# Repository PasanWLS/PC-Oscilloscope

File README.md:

# PC-Oscilloscope
PC Oscilloscope designing
this is our 3rd year final project, pc oscilloscope

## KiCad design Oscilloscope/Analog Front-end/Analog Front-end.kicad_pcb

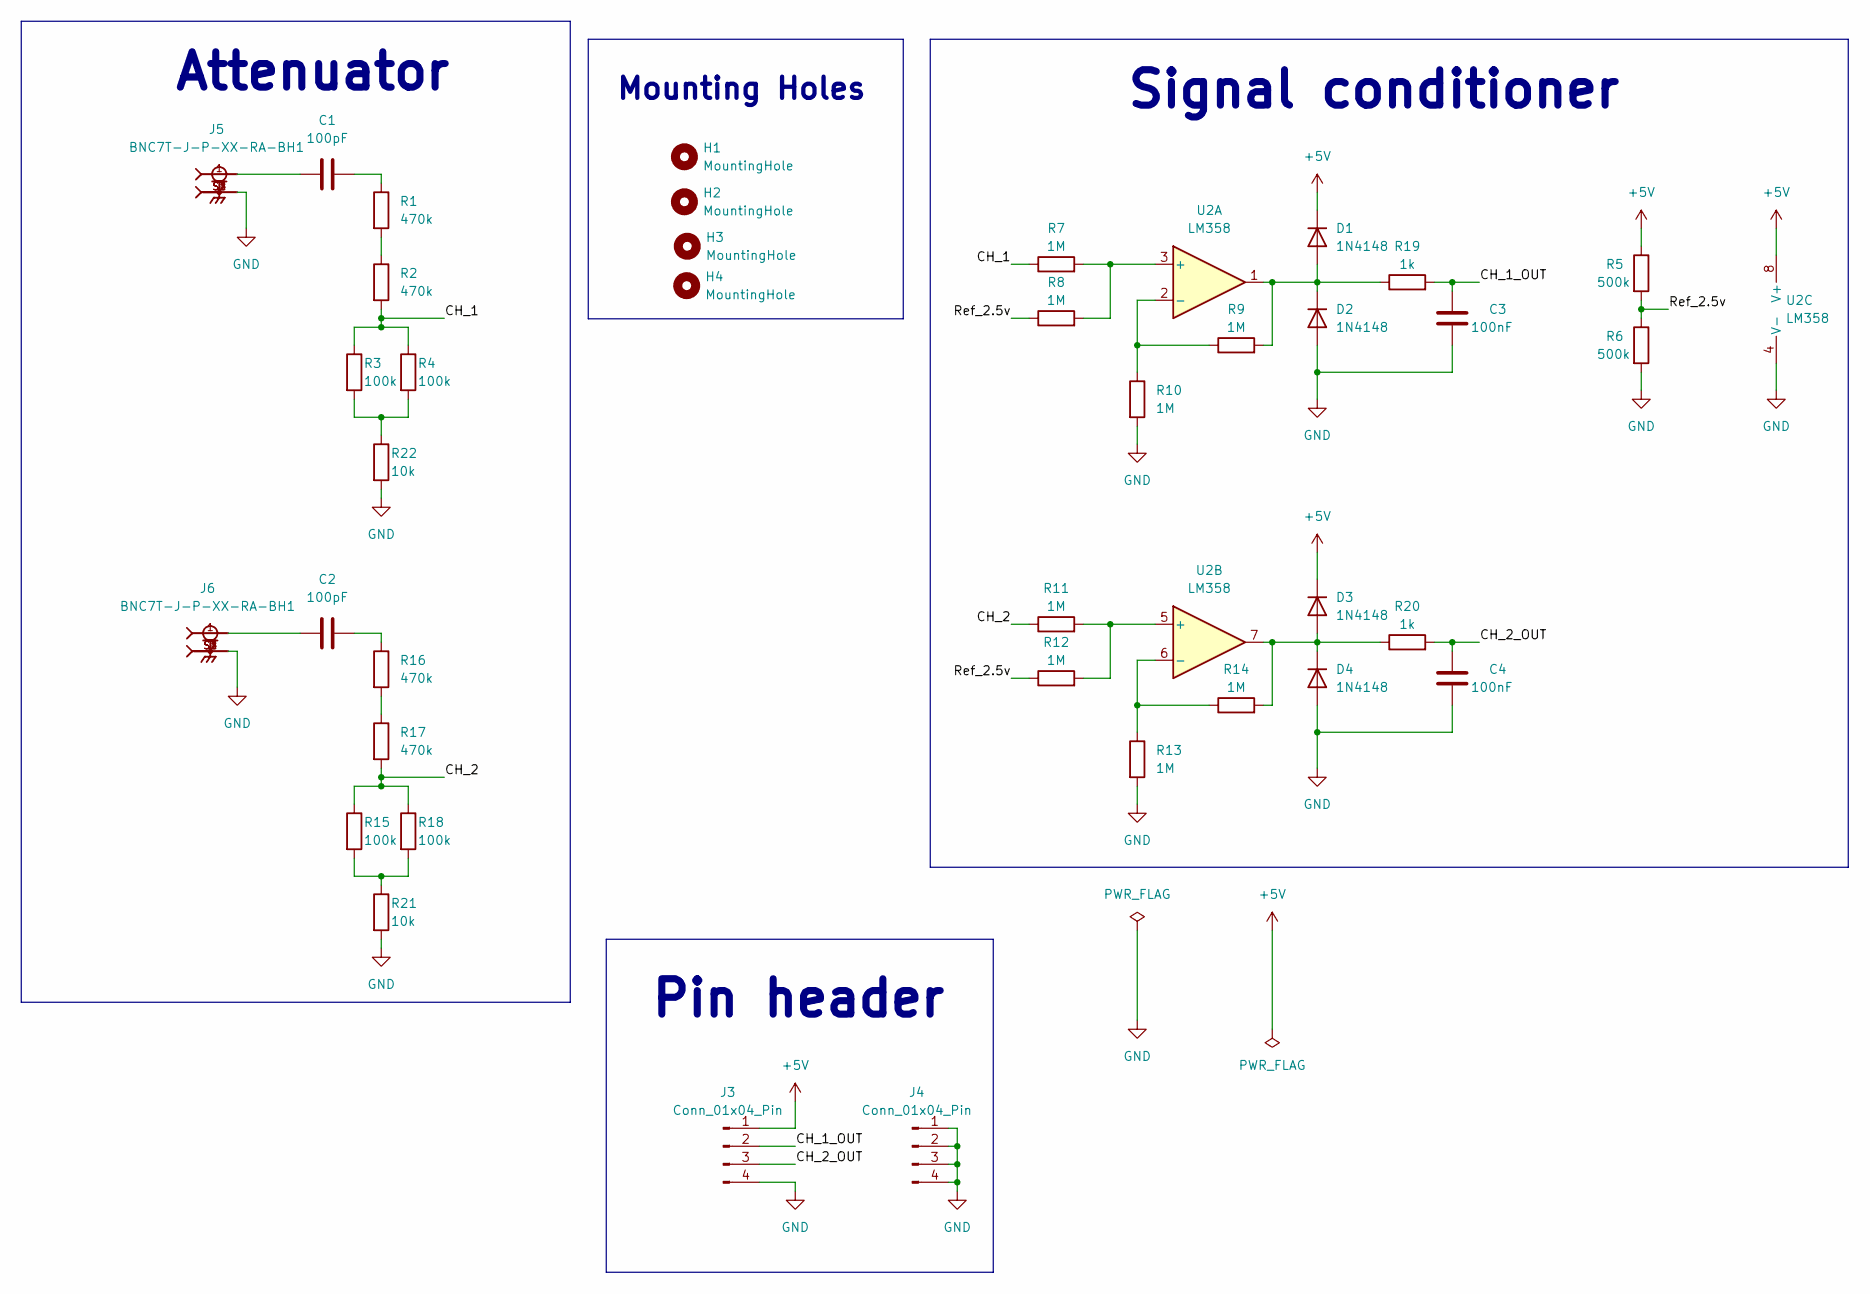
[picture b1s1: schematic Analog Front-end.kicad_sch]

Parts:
C1, C2: 100pF; C_Disc_D3.8mm_W2.6mm_P2.50mm
C3, C4: 100nF; C_Disc_D3.8mm_W2.6mm_P2.50mm
D1, D2, D3, D4: 1N4148; D_DO-35_SOD27_P7.62mm_Horizontal
H1, H2, H3, H4: MountingHole; MountingHole_2.2mm_M2
J3, J4: Conn_01x04_Pin; PinHeader_1x04_P2.54mm_Vertical
J5, J6: BNC7T-J-P-XX-RA-BH1; SAMTEC_BNC7T-J-P-XX-RA-BH1; PARTREV G
R1, R2, R16, R17: 470k; R_Axial_DIN0207_L6.3mm_D2.5mm_P10.16mm_Horizontal
R3, R4, R15, R18: 100k; R_Axial_DIN0207_L6.3mm_D2.5mm_P10.16mm_Horizontal
R5, R6: 500k; R_Axial_DIN0207_L6.3mm_D2.5mm_P10.16mm_Horizontal
R7, R8, R9, R10, R11, R12, R13, R14: 1M; R_Axial_DIN0207_L6.3mm_D2.5mm_P10.16mm_Horizontal
R19, R20: 1k; R_Axial_DIN0207_L6.3mm_D2.5mm_P10.16mm_Horizontal
R21, R22: 10k; R_Axial_DIN0207_L6.3mm_D2.5mm_P10.16mm_Horizontal
U2: LM358; DIP-8_W7.62mm

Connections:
+5V: D1.1 (K), D3.1 (K), J3.1, R5.1, U2.8 (V+)
/CH_1: R2.2, R3.1, R4.1, R7.1
/CH_1_OUT: C3.2, J3.2, R19.2
/CH_2: R11.1, R15.1, R17.2, R18.1
/CH_2_OUT: C4.2, J3.3, R20.2
/Ref_2.5v: R5.2, R6.1, R8.1, R12.1
GND: C3.1, C4.1, D2.2 (A), D4.2 (A), J3.4, J4.1, J4.2, J4.3, J4.4, J5.S1, J5.S2, J5.S3, J5.S4, J6.S1, J6.S2, J6.S3, J6.S4, R6.2, R10.2, R13.2, R21.2, R22.2, U2.4 (V-)
unnamed: C1.1, J5.1
unnamed: C1.2, R1.1
unnamed: C2.1, J6.1
unnamed: C2.2, R16.1
unnamed: D1.2 (A), D2.1 (K), R9.2, R19.1, U2.1
unnamed: D3.2 (A), D4.1 (K), R14.2, R20.1, U2.7
unnamed: R1.2, R2.1
unnamed: R15.2, R18.2, R21.1
unnamed: R16.2, R17.1
unnamed: R3.2, R4.2, R22.1
unnamed: R7.2, R8.2, U2.3 (+)
unnamed: R9.1, R10.1, U2.2 (-)
unnamed: R11.2, R12.2, U2.5 (+)
unnamed: R13.1, R14.1, U2.6 (-)

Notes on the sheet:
Mounting Holes
Signal conditioner
Attenuator
Pin header

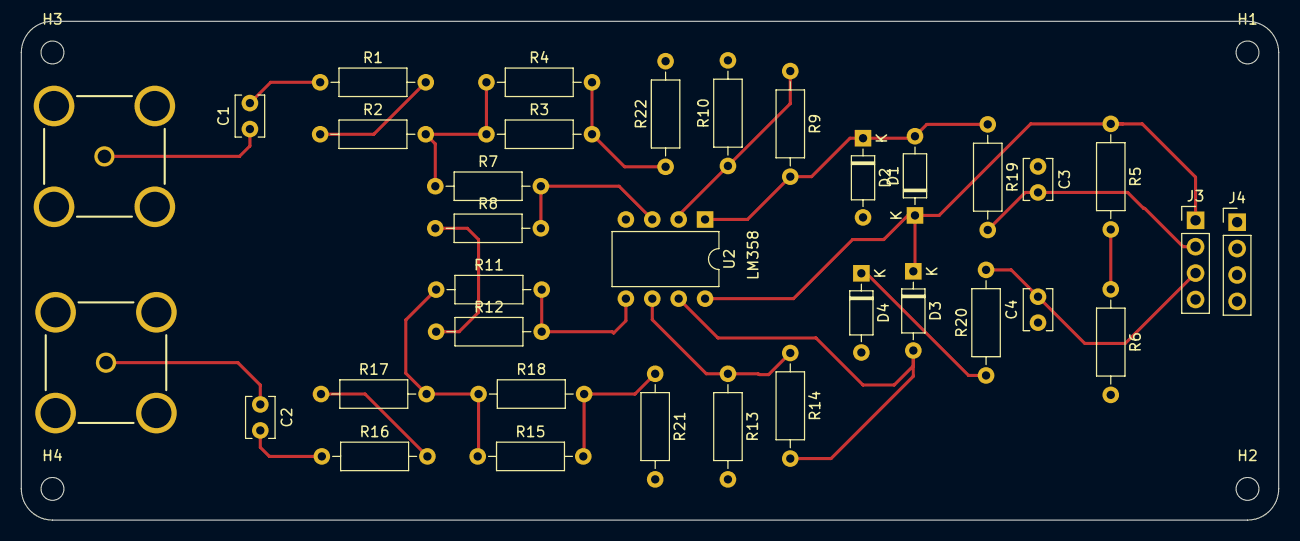
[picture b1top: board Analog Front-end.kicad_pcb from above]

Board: 2 copper layers, 121.0 x 48.0 mm, 39 parts (0 on the bottom side), 21 nets.

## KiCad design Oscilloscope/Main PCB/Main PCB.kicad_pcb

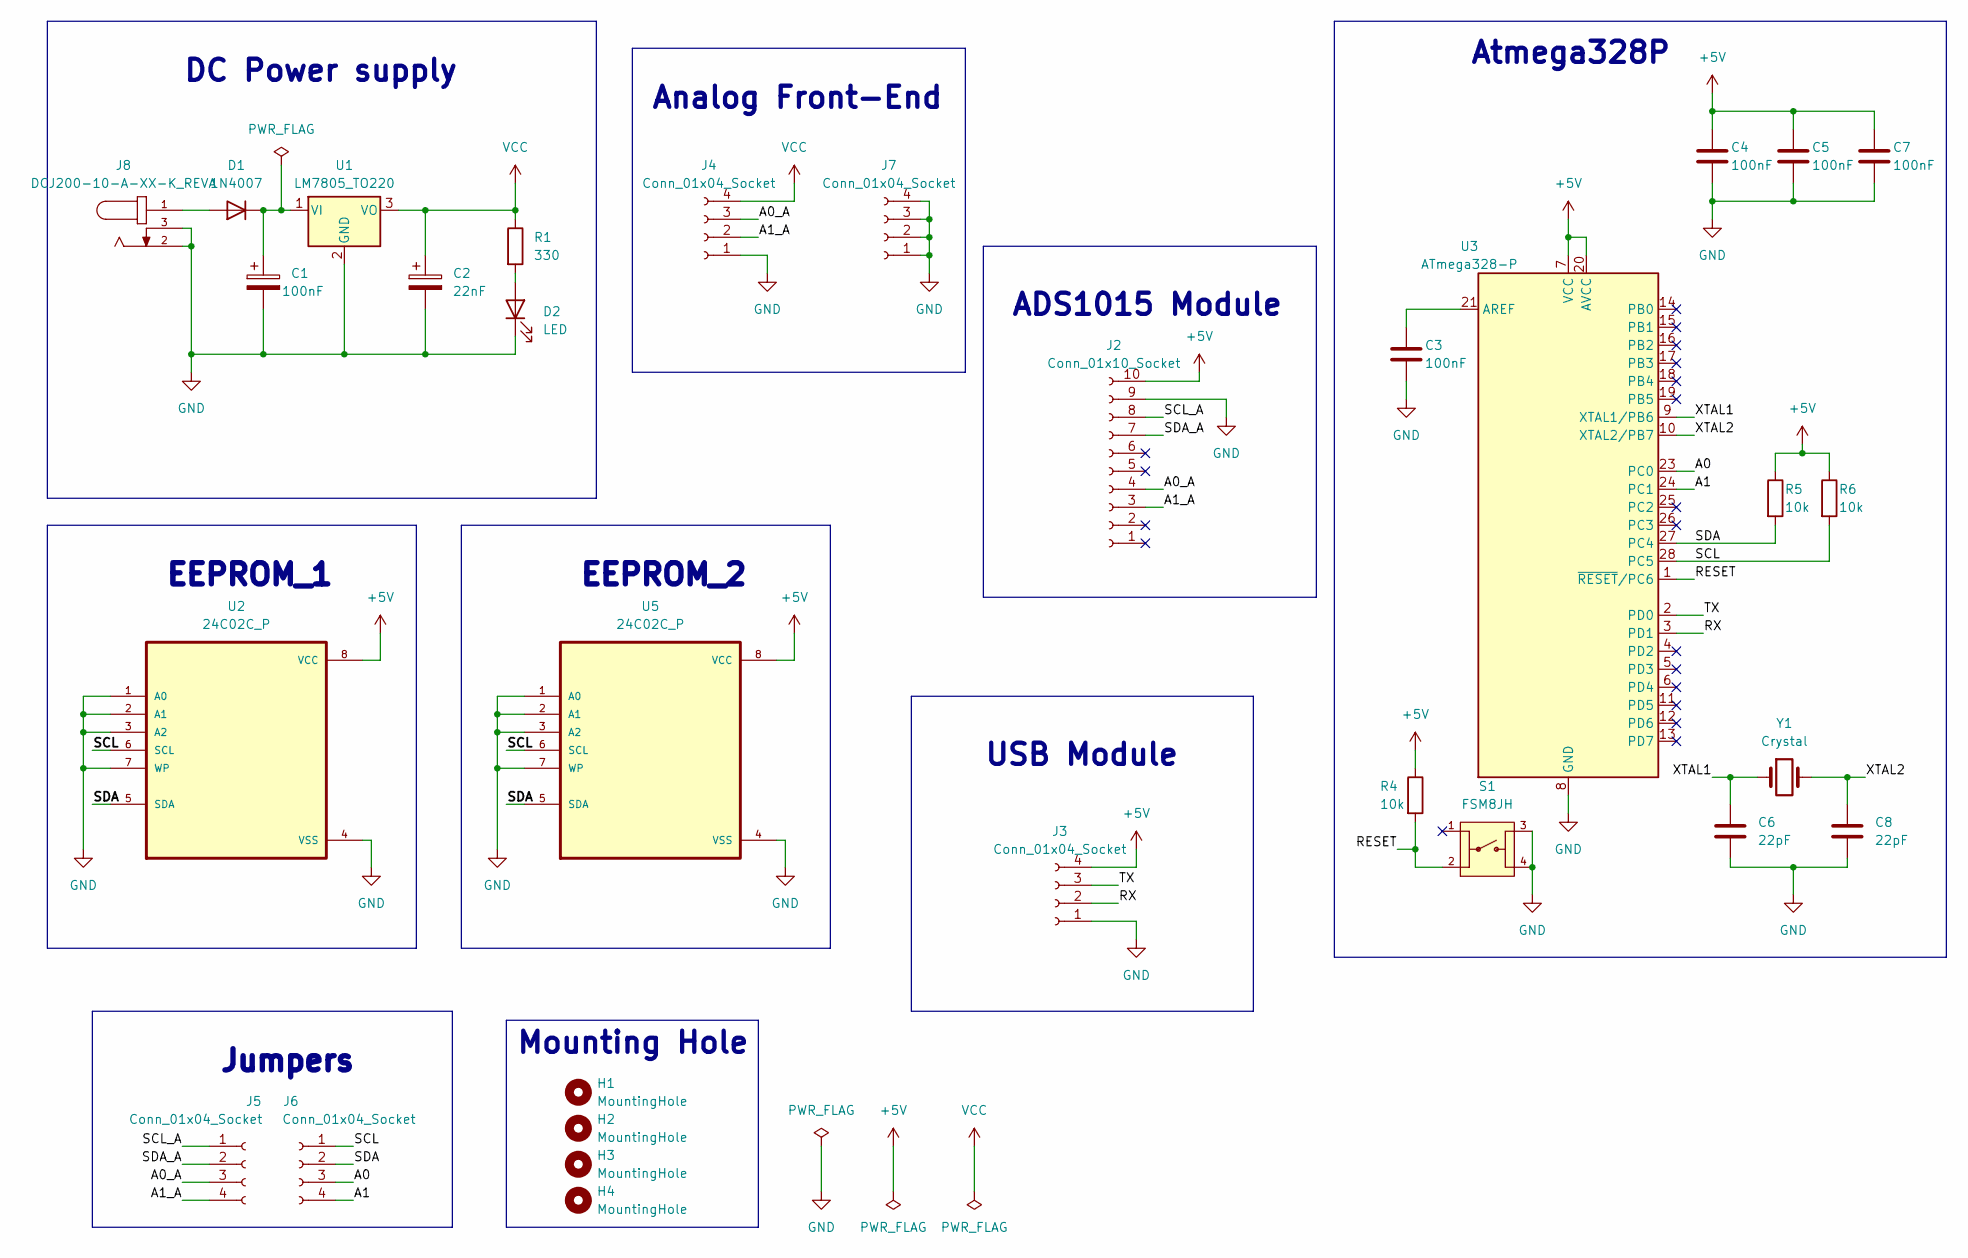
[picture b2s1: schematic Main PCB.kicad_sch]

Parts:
C1: 100nF; CP_Radial_D5.0mm_P2.50mm
C2: 22nF; CP_Radial_D5.0mm_P2.50mm
C3, C4, C5, C7: 100nF; C_Disc_D3.8mm_W2.6mm_P2.50mm
C6, C8: 22pF; C_Disc_D3.4mm_W2.1mm_P2.50mm
D1: 1N4007; D_DO-41_SOD81_P10.16mm_Horizontal
D2: LED; LED_D5.0mm
H1, H2, H3, H4: MountingHole; MountingHole_2.2mm_M2
J2: Conn_01x10_Socket; PinSocket_1x10_P2.54mm_Vertical
J3: Conn_01x04_Socket; PinSocket_1x04_P2.54mm_Vertical
J4, J5, J6, J7: Conn_01x04_Socket; PinHeader_1x04_P2.54mm_Vertical
J8: DCJ200-10-A-XX-K_REVA; GCT_DCJ200-10-A-XX-K_REVA; PARTREV A
R1: 330; R_Axial_DIN0207_L6.3mm_D2.5mm_P10.16mm_Horizontal
R4, R5, R6: 10k; R_Axial_DIN0207_L6.3mm_D2.5mm_P10.16mm_Horizontal
S1: FSM8JH; SW_FSM8JH; PARTREV C10
U1: LM7805_TO220; TO-220-3_Vertical
U2, U5: 24C02C_P; DIP787W46P254L927H533Q8
U3: ATmega328-P; DIP-28_W7.62mm
Y1: Crystal; Resonator-2Pin_W8.0mm_H3.5mm

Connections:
+5V: C4.1, C5.1, C7.1, J2.10, J3.4, R4.1, R5.1, R6.1, U2.8 (VCC), U3.7 (VCC), U3.20 (AVCC), U5.8 (VCC)
/A0: J6.3, U3.23 (PC0)
/A0_A: J2.4, J4.3, J5.3
/A1: J6.4, U3.24 (PC1)
/A1_A: J2.3, J4.2, J5.4
/RESET: R4.2, S1.2, U3.1 (~RESET/PC6)
/RX: J3.2, U3.3 (PD1)
/SCL: J6.1, R6.2, U2.6 (SCL), U3.28 (PC5), U5.6 (SCL)
/SCL_A: J2.8, J5.1
/SDA: J6.2, R5.2, U2.5 (SDA), U3.27 (PC4), U5.5 (SDA)
/SDA_A: J2.7, J5.2
/TX: J3.3, U3.2 (PD0)
/XTAL1: C6.1, U3.9 (XTAL1/PB6), Y1.1
/XTAL2: C8.1, U3.10 (XTAL2/PB7), Y1.2
GND: C1.2, C2.2, C3.2, C4.2, C5.2, C6.2, C7.2, C8.2, D2.1 (K), J2.9, J3.1, J4.1, J7.1, J7.2, J7.3, J7.4, J8.2, J8.3, S1.3, S1.4, U1.2 (GND), U2.1 (A0), U2.2 (A1), U2.3 (A2), U2.4 (VSS), U2.7 (WP), U3.8 (GND), U3.22 (GND), U5.1 (A0), U5.2 (A1), U5.3 (A2), U5.4 (VSS), U5.7 (WP)
unnamed: D1.2 (A), J8.1
unnamed: C1.1, D1.1 (K), U1.1 (VI)
unnamed: D2.2 (A), R1.2
unnamed: C3.1, U3.21 (AREF)
VCC: C2.1, J4.4, R1.1, U1.3 (VO)

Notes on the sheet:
EEPROM_2
Analog Front-End
Atmega328P
USB Module
DC Power supply
EEPROM_1
Jumpers
ADS1015 Module
Mounting Hole

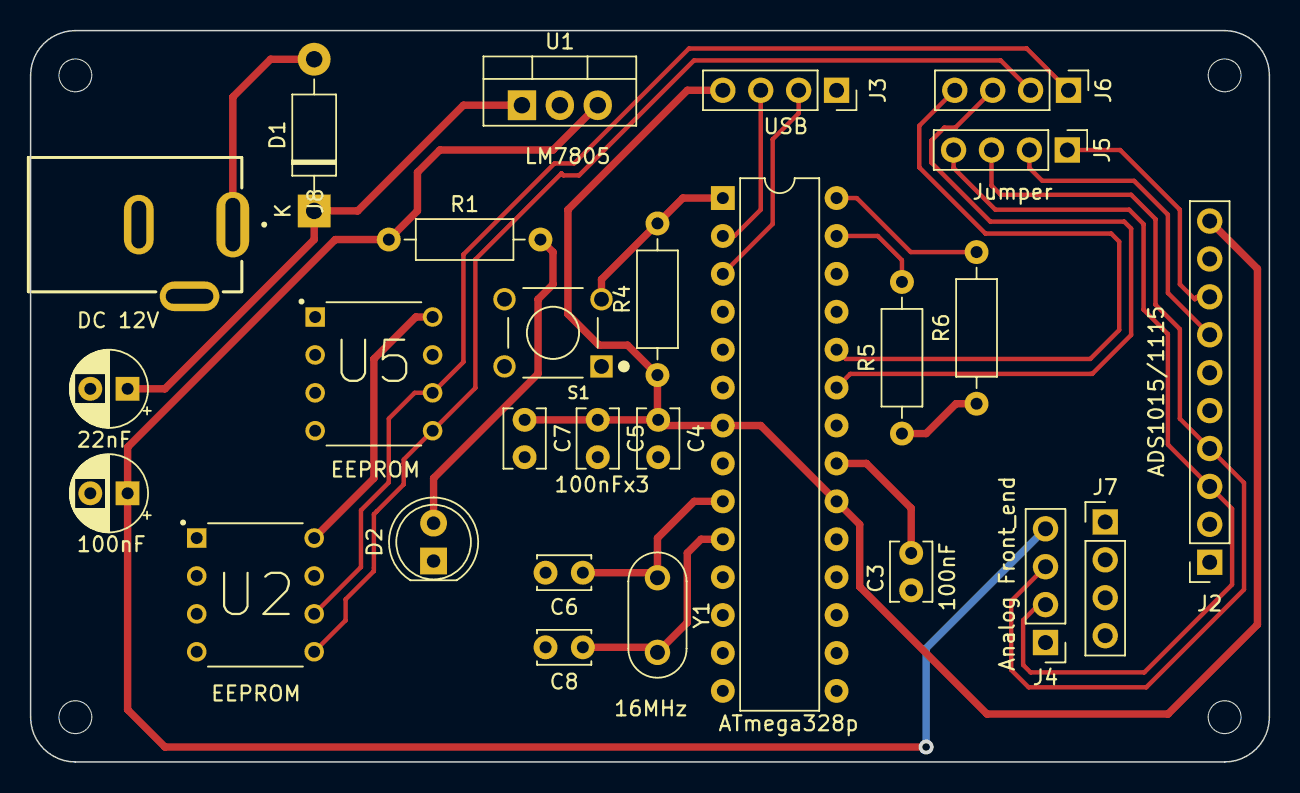
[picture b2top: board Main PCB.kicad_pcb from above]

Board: 2 copper layers, 83.0 x 49.0 mm, 31 parts (0 on the bottom side), 20 nets.

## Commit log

2024-06-17 3rd year final project, pc oscilloscope
